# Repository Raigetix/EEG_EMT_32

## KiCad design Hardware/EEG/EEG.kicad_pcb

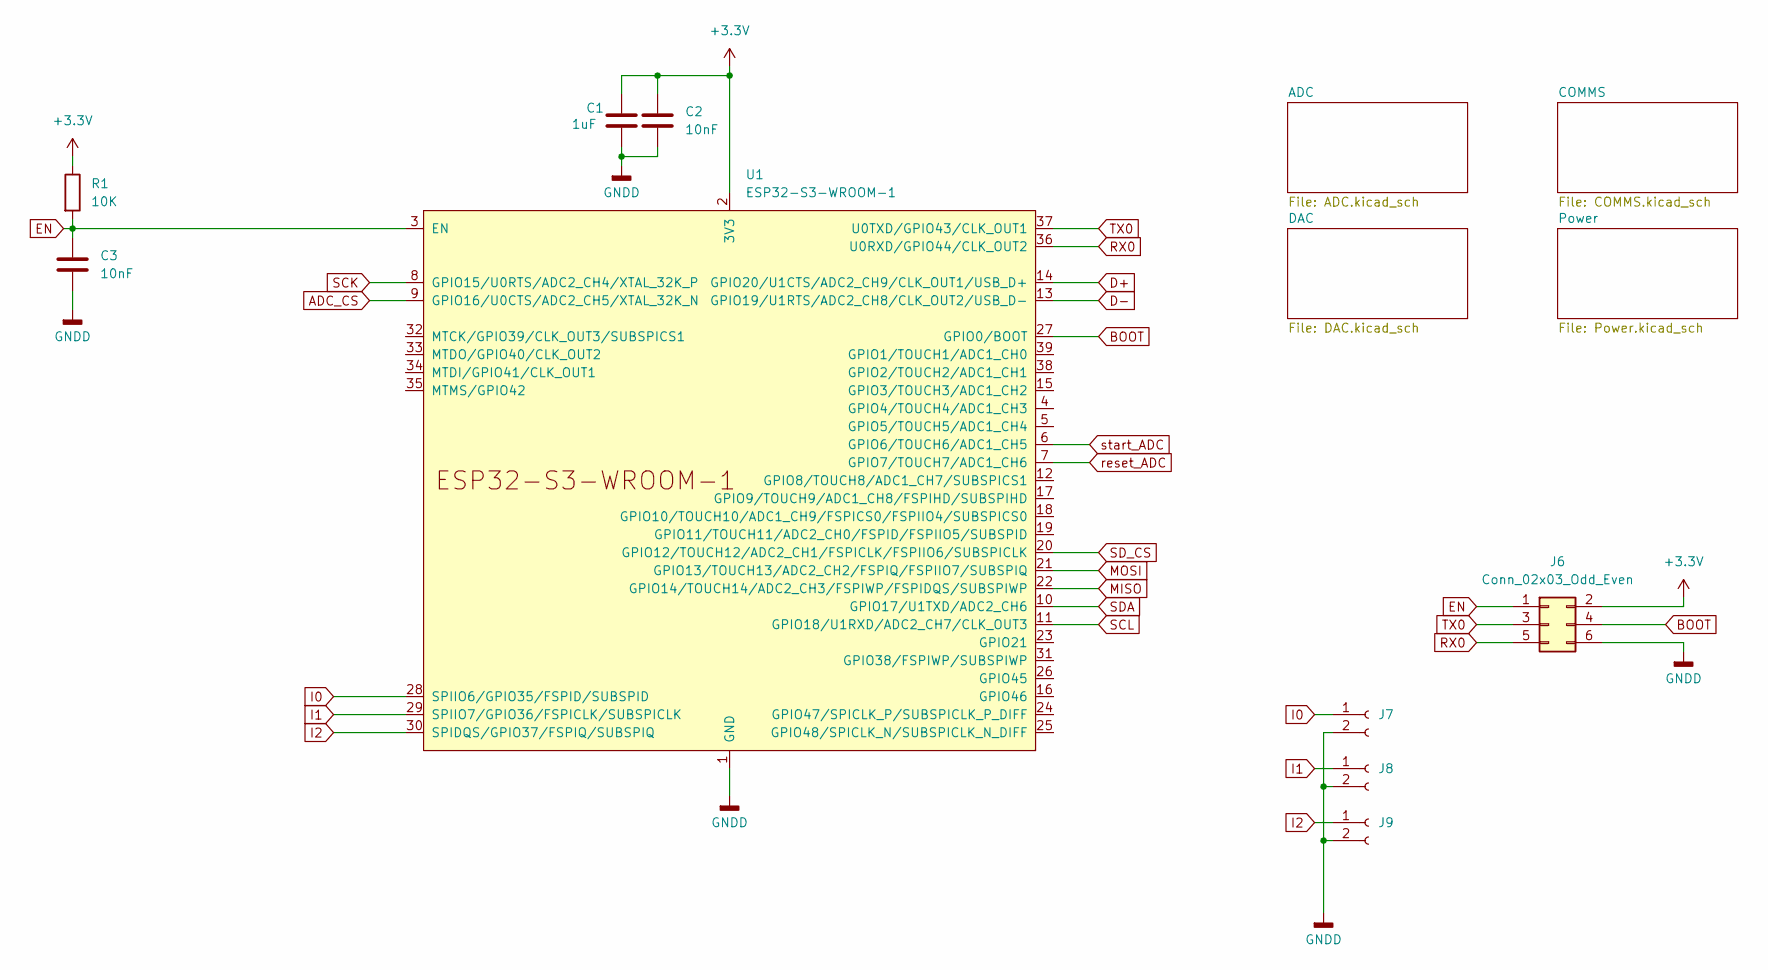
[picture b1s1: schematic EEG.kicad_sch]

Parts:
C1: 1uF; C_1210_3225Metric_Pad1.33x2.70mm_HandSolder
C2, C3: 10nF; C_0603_1608Metric_Pad1.08x0.95mm_HandSolder
J6: Conn_02x03_Odd_Even; PinHeader_2x03_P2.54mm_Vertical
J7, J8, J9: Conn_01x02_Socket; JST_XA_B02B-XASK-1-A_1x02_P2.50mm_Vertical
R1: 10K; R_0402_1005Metric_Pad0.72x0.64mm_HandSolder
U1: ESP32-S3-WROOM-1

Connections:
+3.3V: C1.1, C2.1, J6.2, R1.1, U1.2 (3V3); also elsewhere on the board
ADC_CS: U1.9 (GPIO16/U0CTS/ADC2_CH5/XTAL_32K_N); also elsewhere on the board
BOOT: J6.4, U1.27 (GPIO0/BOOT)
D+: U1.14 (GPIO20/U1CTS/ADC2_CH9/CLK_OUT1/USB_D+); also elsewhere on the board
D-: U1.13 (GPIO19/U1RTS/ADC2_CH8/CLK_OUT2/USB_D-); also elsewhere on the board
EN: C3.1, J6.1, R1.2, U1.3 (EN)
GNDA: C1.2, C2.2, C3.2, J6.6, J7.2, J8.2, J9.2, U1.1 (GND), U1.40 (GND), U1.41 (GND); also elsewhere on the board
I0: J7.1, U1.28 (SPIIO6/GPIO35/FSPID/SUBSPID)
I1: J8.1, U1.29 (SPIIO7/GPIO36/FSPICLK/SUBSPICLK)
I2: J9.1, U1.30 (SPIDQS/GPIO37/FSPIQ/SUBSPIQ)
MISO: U1.22 (GPIO14/TOUCH14/ADC2_CH3/FSPIWP/FSPIDQS/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); also elsewhere on the board
MOSI: U1.21 (GPIO13/TOUCH13/ADC2_CH2/FSPIQ/FSPIIO7/S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); also elsewhere on the board
RX0: J6.5, U1.36 (U0RXD/GPIO44/CLK_OUT2)
SCK: U1.8 (GPIO15/U0RTS/ADC2_CH4/XTAL_32K_P); also elsewhere on the board
SCL: U1.11 (GPIO18/U1RXD/ADC2_CH7/CLK_OUT3); also elsewhere on the board
SDA: U1.10 (GPIO17/U1TXD/ADC2_CH6); also elsewhere on the board
SD_CS: U1.20 (GPIO12/TOUCH12/ADC2_CH1/FSPICLK/FSPIIO6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); also elsewhere on the board
TX0: J6.3, U1.37 (U0TXD/GPIO43/CLK_OUT1)
reset_ADC: U1.7 (GPIO7/TOUCH7/ADC1_CH6); also elsewhere on the board
start_ADC: U1.6 (GPIO6/TOUCH6/ADC1_CH5); also elsewhere on the board

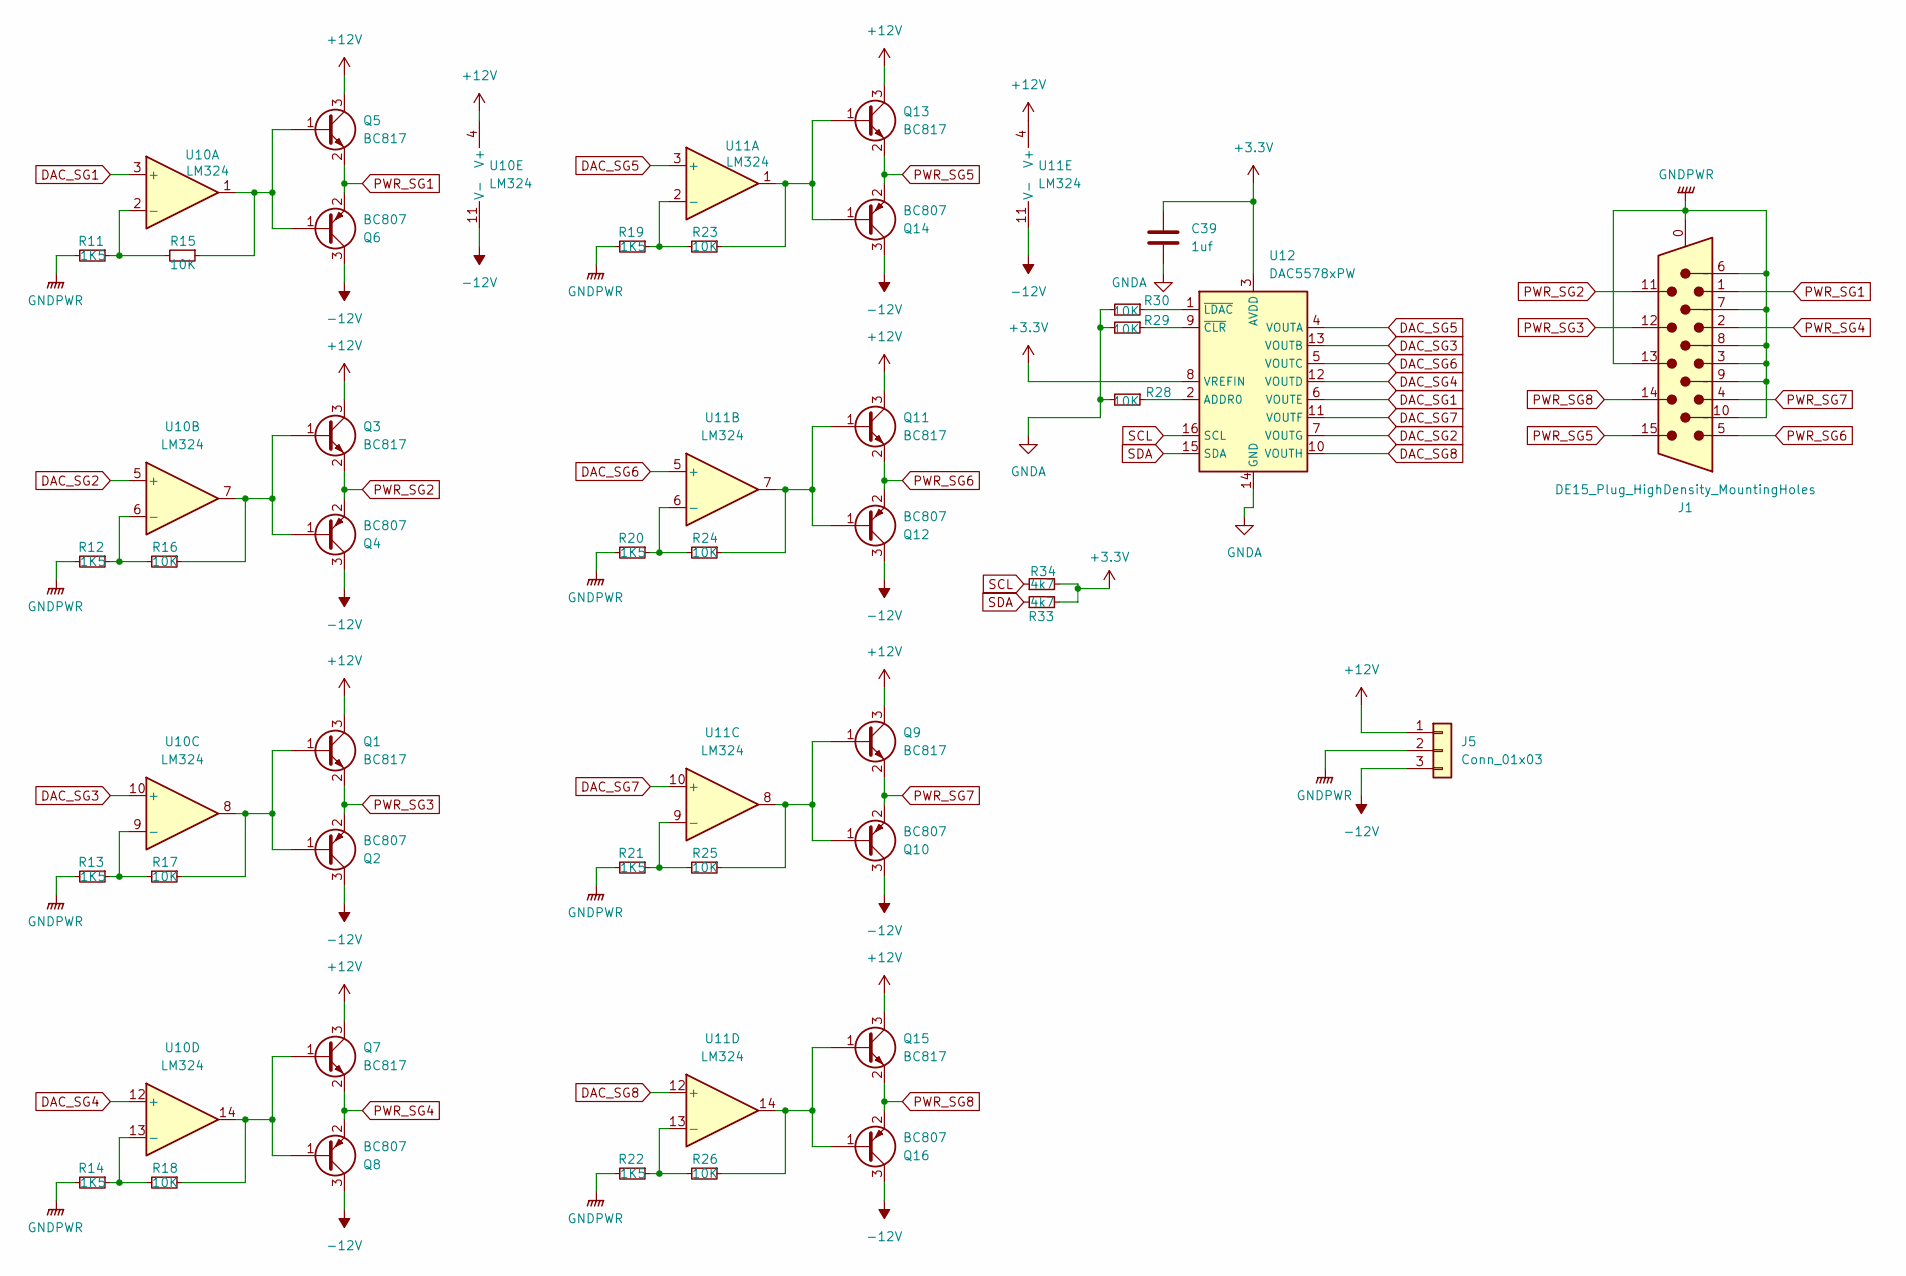
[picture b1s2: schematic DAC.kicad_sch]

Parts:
C39: 1uf; C_0603_1608Metric_Pad1.08x0.95mm_HandSolder
J1: DE15_Plug_HighDensity_MountingHoles; DSUB-15-HD_Female_Horizontal_P2.29x1.98mm_EdgePinOffset3.03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
J5: Conn_01x03; TerminalBlock_Phoenix_MKDS-1,5-3_1x03_P5.00mm_Horizontal
Q1, Q3, Q5, Q7, Q9, Q11, Q13, Q15: BC817; SOT-23
Q2, Q4, Q6, Q8, Q10, Q12, Q14, Q16: BC807; SOT-23
R11, R12, R13, R14, R19, R20, R21, R22: 1K5; R_0402_1005Metric_Pad0.72x0.64mm_HandSolder
R15, R16, R17, R18, R23, R24, R25, R26, R28, R29, R30: 10K; R_0402_1005Metric_Pad0.72x0.64mm_HandSolder
R33, R34: 4k7; R_0402_1005Metric_Pad0.72x0.64mm_HandSolder
U10, U11: LM324; TSSOP-14_4.4x5mm_P0.65mm
U12: DAC5578xPW; TSSOP-16_4.4x5mm_P0.65mm

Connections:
+3.3V: C39.1, R33.2, R34.2, U12.3 (AVDD), U12.8 (VREFIN); also elsewhere on the board
+12V: J5.1, Q1.3 (C), Q3.3 (C), Q5.3 (C), Q7.3 (C), Q9.3 (C), Q11.3 (C), Q13.3 (C), Q15.3 (C), U10.4 (V+), U11.4 (V+)
-12V: J5.3, Q2.3 (C), Q4.3 (C), Q6.3 (C), Q8.3 (C), Q10.3 (C), Q12.3 (C), Q14.3 (C), Q16.3 (C), U10.11 (V-), U11.11 (V-)
DAC_SG1: U10.3 (+), U12.6 (VOUTE)
DAC_SG2: U10.5 (+), U12.7 (VOUTG)
DAC_SG3: U10.10 (+), U12.13 (VOUTB)
DAC_SG4: U10.12 (+), U12.12 (VOUTD)
DAC_SG5: U11.3 (+), U12.4 (VOUTA)
DAC_SG6: U11.5 (+), U12.5 (VOUTC)
DAC_SG7: U11.10 (+), U12.11 (VOUTF)
DAC_SG8: U11.12 (+), U12.10 (VOUTH)
GNDA: C39.2, J1.0, J1.3, J1.6, J1.7, J1.8, J1.9, J1.10, J1.13, J5.2, R11.2, R12.2, R13.2, R14.2, R19.2, R20.2, R21.2, R22.2, R28.2, R29.2, R30.2, U12.14 (GND); also elsewhere on the board
unnamed: Q1.1 (B), Q2.1 (B), R17.1, U10.8
unnamed: Q3.1 (B), Q4.1 (B), R16.1, U10.7
unnamed: Q5.1 (B), Q6.1 (B), R15.1, U10.1
unnamed: Q7.1 (B), Q8.1 (B), R18.1, U10.14
unnamed: Q9.1 (B), Q10.1 (B), R25.1, U11.8
unnamed: Q11.1 (B), Q12.1 (B), R24.1, U11.7
unnamed: Q13.1 (B), Q14.1 (B), R23.1, U11.1
unnamed: Q15.1 (B), Q16.1 (B), R26.1, U11.14
unnamed: R11.1, R15.2, U10.2 (-)
unnamed: R12.1, R16.2, U10.6 (-)
unnamed: R13.1, R17.2, U10.9 (-)
unnamed: R14.1, R18.2, U10.13 (-)
unnamed: R19.1, R23.2, U11.2 (-)
unnamed: R20.1, R24.2, U11.6 (-)
unnamed: R21.1, R25.2, U11.9 (-)
unnamed: R22.1, R26.2, U11.13 (-)
unnamed: R28.1, U12.2 (ADDR0)
unnamed: R29.1, U12.9 (~CLR)
unnamed: R30.1, U12.1 (~LDAC)
PWR_SG1: J1.1, Q5.2 (E), Q6.2 (E)
PWR_SG2: J1.11, Q3.2 (E), Q4.2 (E)
PWR_SG3: J1.12, Q1.2 (E), Q2.2 (E)
PWR_SG4: J1.2, Q7.2 (E), Q8.2 (E)
PWR_SG5: J1.15, Q13.2 (E), Q14.2 (E)
PWR_SG6: J1.5, Q11.2 (E), Q12.2 (E)
PWR_SG7: J1.4, Q9.2 (E), Q10.2 (E)
PWR_SG8: J1.14, Q15.2 (E), Q16.2 (E)
SCL: R34.1, U12.16 (SCL); also elsewhere on the board
SDA: R33.1, U12.15 (SDA); also elsewhere on the board

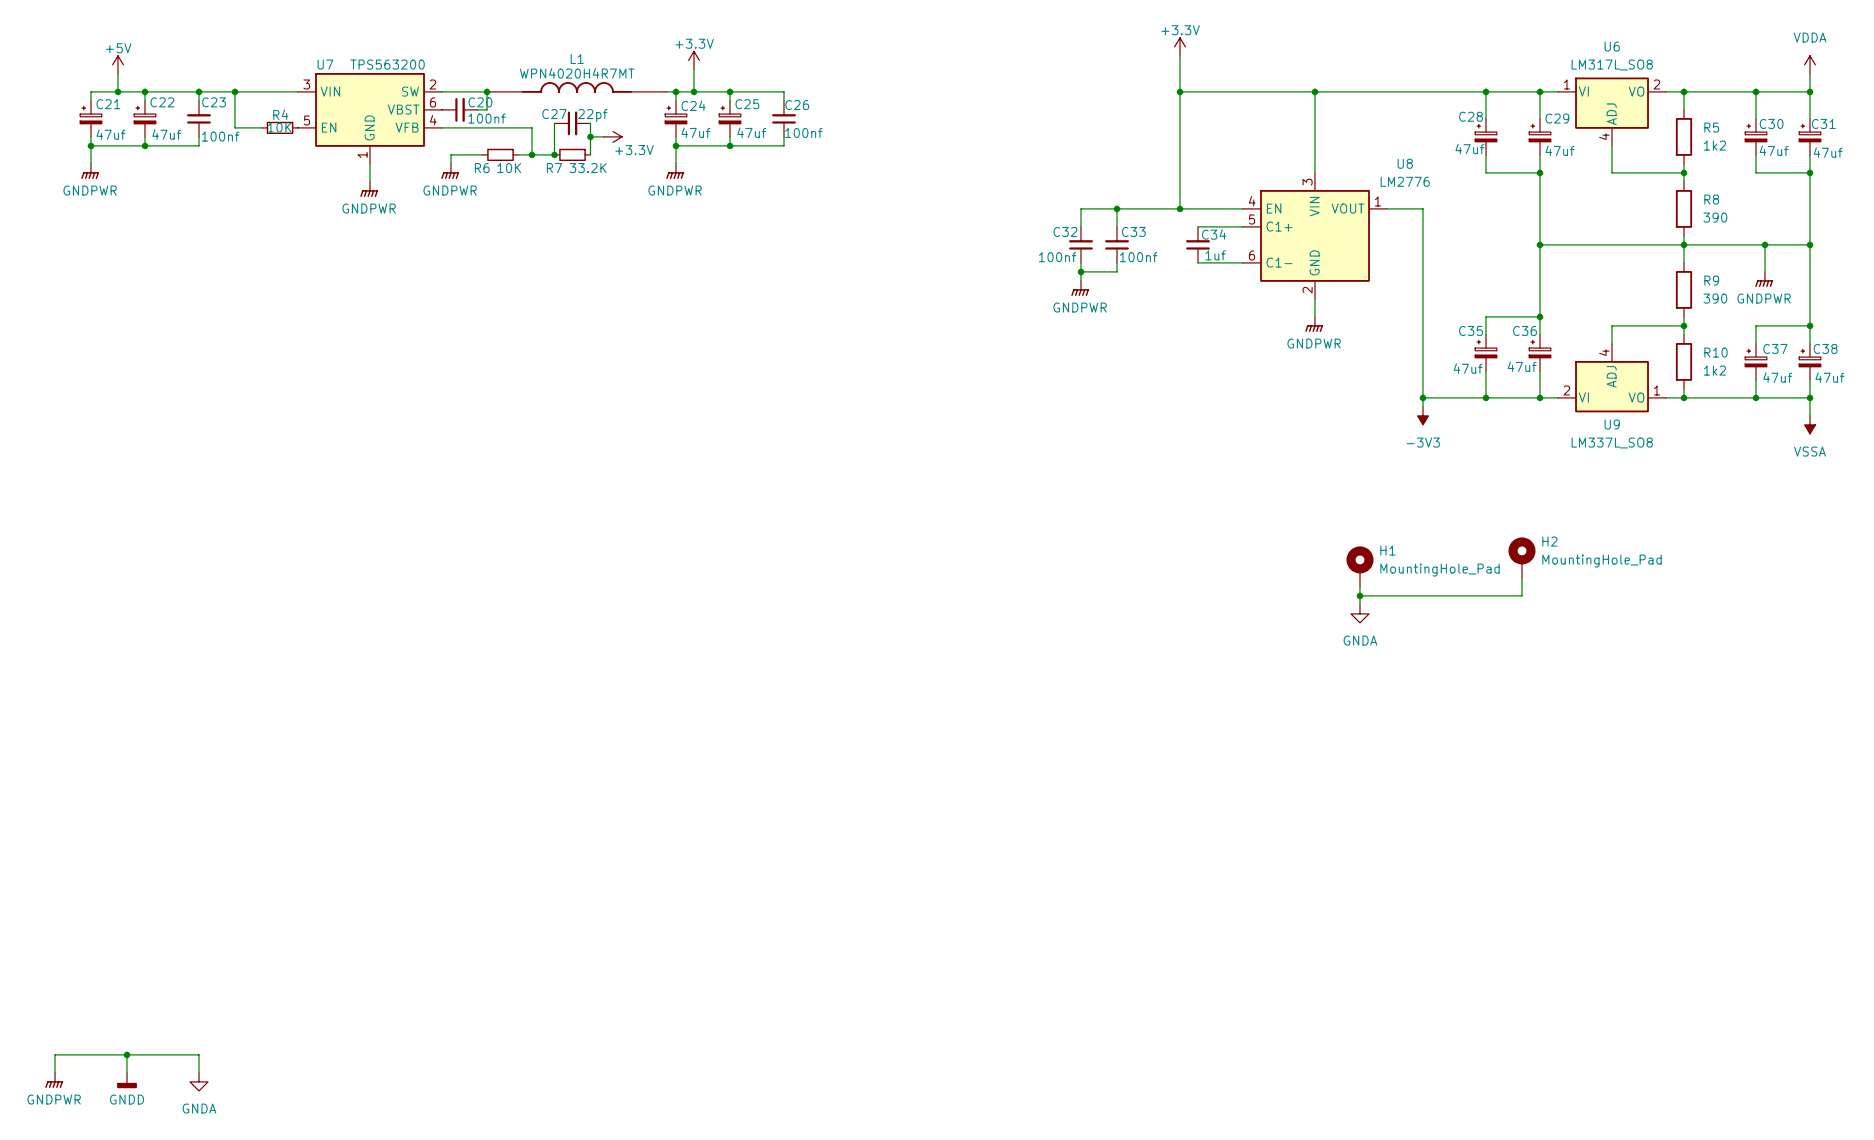
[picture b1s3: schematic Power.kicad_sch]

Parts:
C20, C23, C26, C32, C33: 100nf; L_0402_1005Metric_Pad0.77x0.64mm_HandSolder
C21, C22, C24, C25, C28, C29, C30, C31, C35, C36, C37, C38: 47uf; C_1210_3225Metric_Pad1.33x2.70mm_HandSolder
C27: 22pf; L_0402_1005Metric_Pad0.77x0.64mm_HandSolder
C34: 1uf; L_0402_1005Metric_Pad0.77x0.64mm_HandSolder
H1, H2: MountingHole_Pad; MountingHole_3.2mm_M3_Pad_Via
L1: WPN4020H4R7MT; L_Vishay_IFSC-1515AH_4x4x1.8mm; PARTREV 1
R4, R6: 10K; R_0402_1005Metric_Pad0.72x0.64mm_HandSolder
R5, R10: 1k2; R_0603_1608Metric_Pad0.98x0.95mm_HandSolder
R7: 33.2K; R_0402_1005Metric_Pad0.72x0.64mm_HandSolder
R8, R9: 390; R_0603_1608Metric_Pad0.98x0.95mm_HandSolder
U6: LM317L_SO8; SOIC-8_3.9x4.9mm_P1.27mm
U7: TPS563200; SOT-23-6
U8: LM2776; SOT-23-6
U9: LM337L_SO8; SOIC-8_3.9x4.9mm_P1.27mm

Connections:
+3.3V: C24.1, C25.1, C26.2, C27.2, C28.1, C29.1, C32.2, C33.2, L1.2, R7.1, U6.1 (VI), U8.3 (VIN), U8.4 (EN); also elsewhere on the board
+5V: C21.1, C22.1, C23.2, R4.2, U7.3 (VIN); also elsewhere on the board
-3V3: C35.2, C36.2, U8.1 (VOUT), U9.2 (VI), U9.3 (VI), U9.6 (VI), U9.7 (VI)
GNDA: C21.2, C22.2, C23.1, C24.2, C25.2, C26.1, C28.2, C29.2, C30.2, C31.2, C32.1, C33.1, C35.1, C36.1, C37.1, C38.1, H1.1, H2.1, R6.2, R8.2, R9.1, U7.1 (GND), U8.2 (GND); also elsewhere on the board
unnamed: R5.2, R8.1, U6.4 (ADJ)
unnamed: R4.1, U7.5 (EN)
unnamed: C20.2, L1.1, U7.2 (SW)
unnamed: C20.1, U7.6 (VBST)
unnamed: C27.1, R6.1, R7.2, U7.4 (VFB)
unnamed: C34.2, U8.5 (C1+)
unnamed: C34.1, U8.6 (C1-)
unnamed: R9.2, R10.1, U9.4 (ADJ)
VDDA: C30.1, C31.1, R5.1, U6.2 (VO), U6.3 (VO), U6.6 (VO), U6.7 (VO); also elsewhere on the board
VSSA: C37.2, C38.2, R10.2, U9.1 (VO); also elsewhere on the board

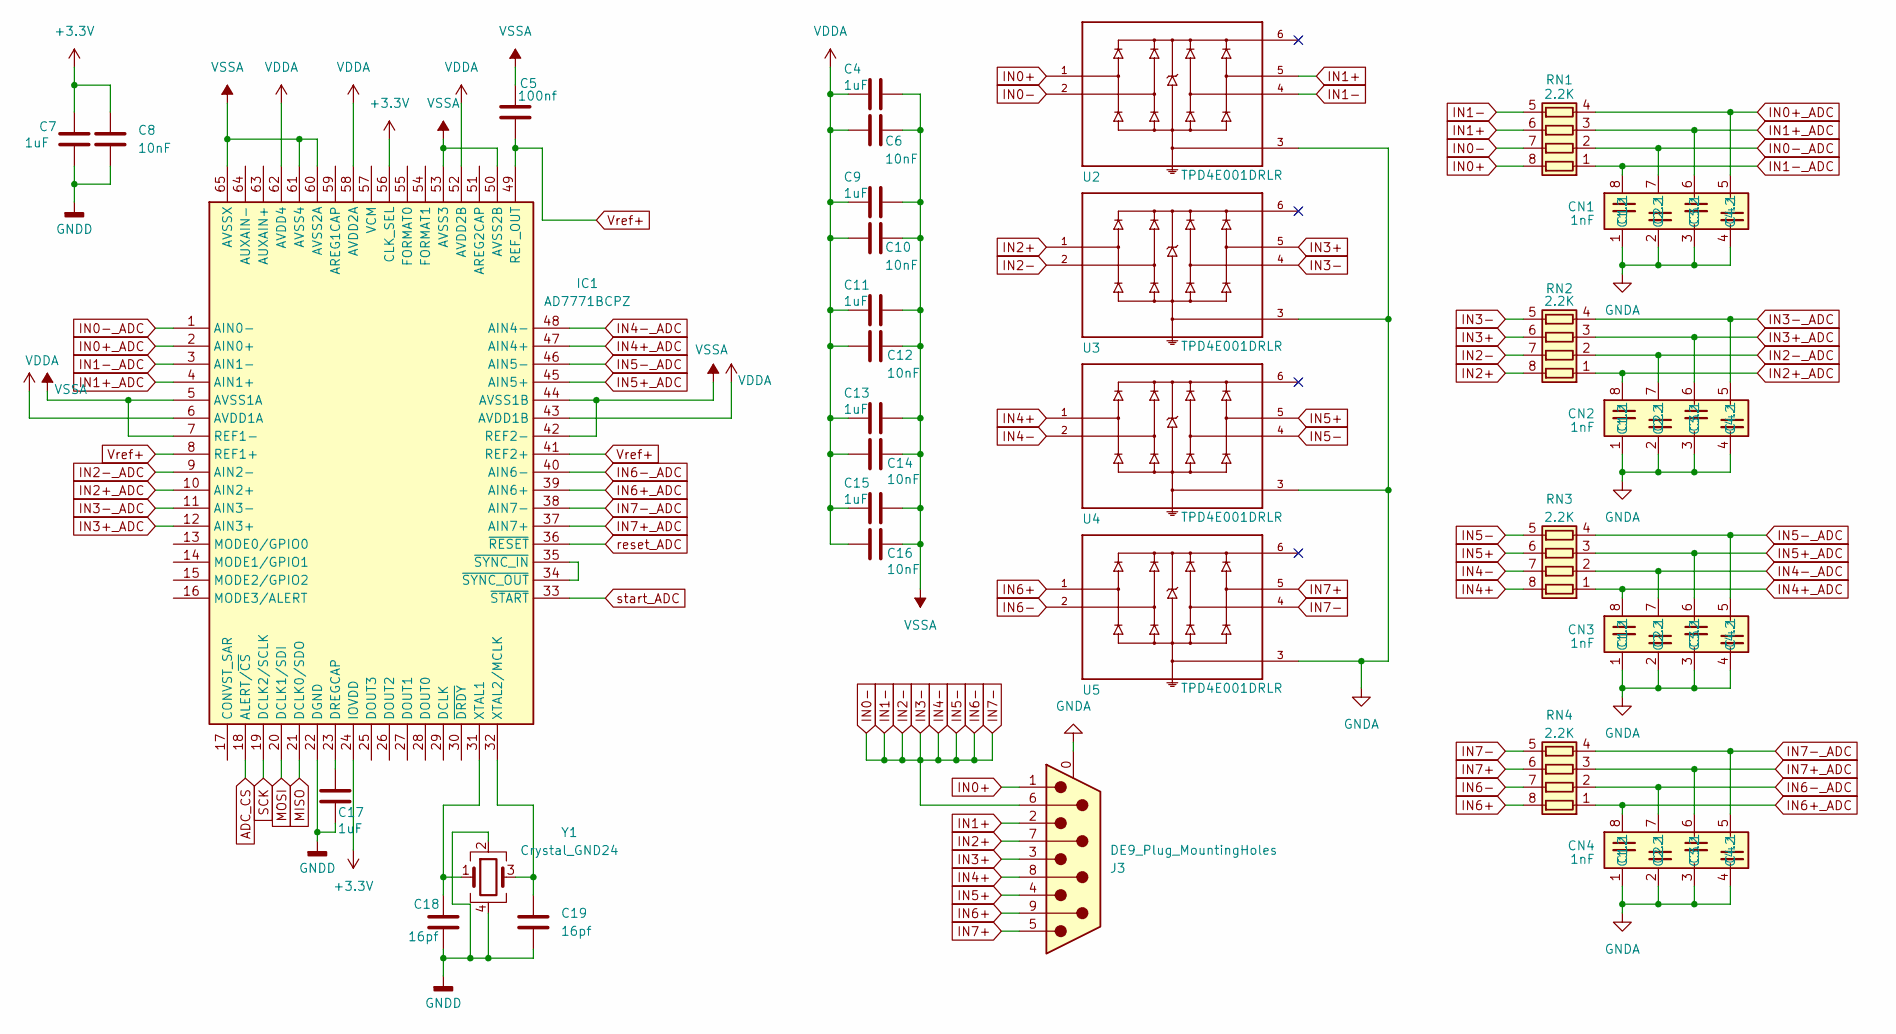
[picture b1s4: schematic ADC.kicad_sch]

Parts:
C4, C9, C11, C13, C15, C17: 1uF; C_0603_1608Metric_Pad1.08x0.95mm_HandSolder
C5: 100nf; C_0402_1005Metric_Pad0.74x0.62mm_HandSolder
C6, C8, C10, C12, C14, C16: 10nF; C_0603_1608Metric_Pad1.08x0.95mm_HandSolder
C7: 1uF; C_1210_3225Metric_Pad1.33x2.70mm_HandSolder
C18, C19: 16pf; C_0402_1005Metric_Pad0.74x0.62mm_HandSolder
CN1: 1nF; R_Array_Convex_4x0603
CN2, CN3, CN4: 1nF; R_Array_Concave_4x0603
IC1: AD7771BCPZ; QFN-64-1EP_9x9mm_P0.5mm_EP7.35x7.35mm; Manufacturer_Part_Number AD7771BCPZ; Mouser Part Number 584-AD7771BCPZ
J3: DE9_Plug_MountingHoles; DSUB-9_Female_Horizontal_P2.77x2.84mm_EdgePinOffset4.94mm_H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
RN1, RN2, RN3, RN4: 2.2K; R_Array_Concave_4x0603
U2, U3, U4, U5: TPD4E001DRLR; Texas_R-PDSO-N6_DRL-6
Y1: Crystal_GND24; Crystal_SMD_SeikoEpson_FA238V-4Pin_3.2x2.5mm

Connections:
+3.3V: C7.1, C8.1, IC1.24 (IOVDD), IC1.56 (CLK_SEL); also elsewhere on the board
ADC_CS: IC1.18 (ALERT/~CS); also elsewhere on the board
GNDA: C7.2, C8.2, C17.2, C18.2, C19.2, CN1.1 (C1.1), CN1.2 (C2.1), CN1.3 (C3.1), CN1.4 (C4.1), CN2.1 (C1.1), CN2.2 (C2.1), CN2.3 (C3.1), CN2.4 (C4.1), CN3.1 (C1.1), CN3.2 (C2.1), CN3.3 (C3.1), CN3.4 (C4.1), CN4.1 (C1.1), CN4.2 (C2.1), CN4.3 (C3.1), CN4.4 (C4.1), IC1.22 (DGND), J3.0 (PAD), U2.3, U3.3, U4.3, U5.3, Y1.2, Y1.4; also elsewhere on the board
IN0+: J3.1, RN1.8 (R1.2), U2.1
IN0+_ADC: CN1.5 (C4.2), IC1.2 (AIN0+), RN1.4 (R4.1)
IN0-: J3.6, RN1.5 (R4.2), RN1.7 (R2.2), RN2.5 (R4.2), RN2.7 (R2.2), RN3.5 (R4.2), RN3.7 (R2.2), RN4.5 (R4.2), RN4.7 (R2.2), U2.2, U2.4, U3.2, U3.4, U4.2, U4.4, U5.2, U5.4
IN0-_ADC: CN1.7 (C2.2), IC1.1 (AIN0-), RN1.2 (R2.1)
IN1+: J3.2, RN1.6 (R3.2), U2.5
IN1+_ADC: CN1.6 (C3.2), IC1.4 (AIN1+), RN1.3 (R3.1)
IN1-_ADC: CN1.8 (C1.2), IC1.3 (AIN1-), RN1.1 (R1.1)
IN2+: J3.7, RN2.8 (R1.2), U3.1
IN2+_ADC: CN2.8 (C1.2), IC1.10 (AIN2+), RN2.1 (R1.1)
IN2-_ADC: CN2.7 (C2.2), IC1.9 (AIN2-), RN2.2 (R2.1)
IN3+: J3.3, RN2.6 (R3.2), U3.5
IN3+_ADC: CN2.6 (C3.2), IC1.12 (AIN3+), RN2.3 (R3.1)
IN3-_ADC: CN2.5 (C4.2), IC1.11 (AIN3-), RN2.4 (R4.1)
IN4+: J3.8, RN3.8 (R1.2), U4.1
IN4+_ADC: CN3.8 (C1.2), IC1.47 (AIN4+), RN3.1 (R1.1)
IN4-_ADC: CN3.7 (C2.2), IC1.48 (AIN4-), RN3.2 (R2.1)
IN5+: J3.4, RN3.6 (R3.2), U4.5
IN5+_ADC: CN3.6 (C3.2), IC1.45 (AIN5+), RN3.3 (R3.1)
IN5-_ADC: CN3.5 (C4.2), IC1.46 (AIN5-), RN3.4 (R4.1)
IN6+: J3.9, RN4.8 (R1.2), U5.1
IN6+_ADC: CN4.8 (C1.2), IC1.39 (AIN6+), RN4.1 (R1.1)
IN6-_ADC: CN4.7 (C2.2), IC1.40 (AIN6-), RN4.2 (R2.1)
IN7+: J3.5, RN4.6 (R3.2), U5.5
IN7+_ADC: CN4.6 (C3.2), IC1.37 (AIN7+), RN4.3 (R3.1)
IN7-_ADC: CN4.5 (C4.2), IC1.38 (AIN7-), RN4.4 (R4.1)
MISO: IC1.21 (DCLK0/SDO); also elsewhere on the board
MOSI: IC1.20 (DCLK1/SDI); also elsewhere on the board
unnamed: C17.1, IC1.23 (DREGCAP)
unnamed: C18.1, IC1.31 (XTAL1), Y1.1
unnamed: C19.1, IC1.32 (XTAL2/MCLK), Y1.3
unnamed: IC1.34 (~SYNC_OUT), IC1.35 (~SYNC_IN)
SCK: IC1.19 (DCLK2/SCLK); also elsewhere on the board
VDDA: C4.2, C6.2, C9.2, C10.2, C11.2, C12.2, C13.2, C14.2, C15.2, C16.2, IC1.6 (AVDD1A), IC1.43 (AVDD1B), IC1.52 (AVDD2B), IC1.58 (AVDD2A), IC1.62 (AVDD4); also elsewhere on the board
VSSA: C4.1, C5.1, C6.1, C9.1, C10.1, C11.1, C12.1, C13.1, C14.1, C15.1, C16.1, IC1.5 (AVSS1A), IC1.7 (REF1-), IC1.42 (REF2-), IC1.44 (AVSS1B), IC1.50 (AVSS2B), IC1.53 (AVSS3), IC1.60 (AVSS2A), IC1.61 (AVSS4), IC1.65 (AVSSX); also elsewhere on the board
Vref+: C5.2, IC1.8 (REF1+), IC1.41 (REF2+), IC1.49 (REF_OUT)
reset_ADC: IC1.36 (~RESET); also elsewhere on the board
start_ADC: IC1.33 (~START); also elsewhere on the board

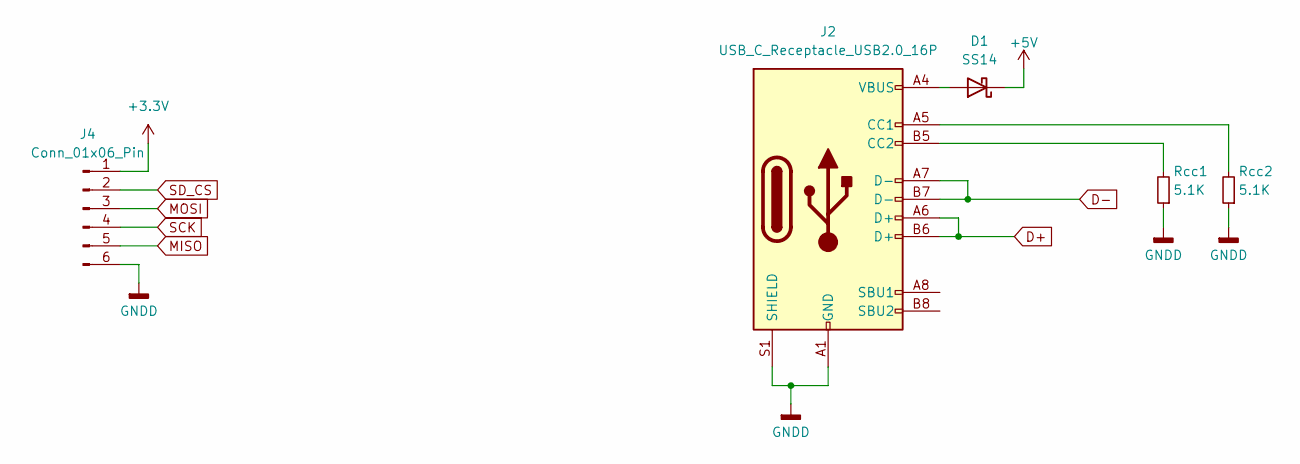
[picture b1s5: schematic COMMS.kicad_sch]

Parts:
D1: SS14; D_SMA
J2: USB_C_Receptacle_USB2.0_16P; USB_C_Receptacle_Palconn_UTC16-G
J4: Conn_01x06_Pin; PinHeader_1x06_P2.54mm_Vertical
Rcc1, Rcc2: 5.1K; R_0402_1005Metric_Pad0.72x0.64mm_HandSolder

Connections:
+3.3V: J4.1; also elsewhere on the board
+5V: D1.1 (K); also elsewhere on the board
D+: J2.A6 (D+), J2.B6 (D+); also elsewhere on the board
D-: J2.A7 (D-), J2.B7 (D-); also elsewhere on the board
GNDA: J2.A1 (GND), J2.A12 (GND), J2.B1 (GND), J2.B12 (GND), J2.S1 (SHIELD), J4.6, Rcc1.1, Rcc2.1; also elsewhere on the board
MISO: J4.5; also elsewhere on the board
MOSI: J4.3; also elsewhere on the board
unnamed: D1.2 (A), J2.A4 (VBUS), J2.A9 (VBUS), J2.B4 (VBUS), J2.B9 (VBUS)
unnamed: J2.A5 (CC1), Rcc2.2
unnamed: J2.B5 (CC2), Rcc1.2
SCK: J4.4; also elsewhere on the board
SD_CS: J4.2; also elsewhere on the board

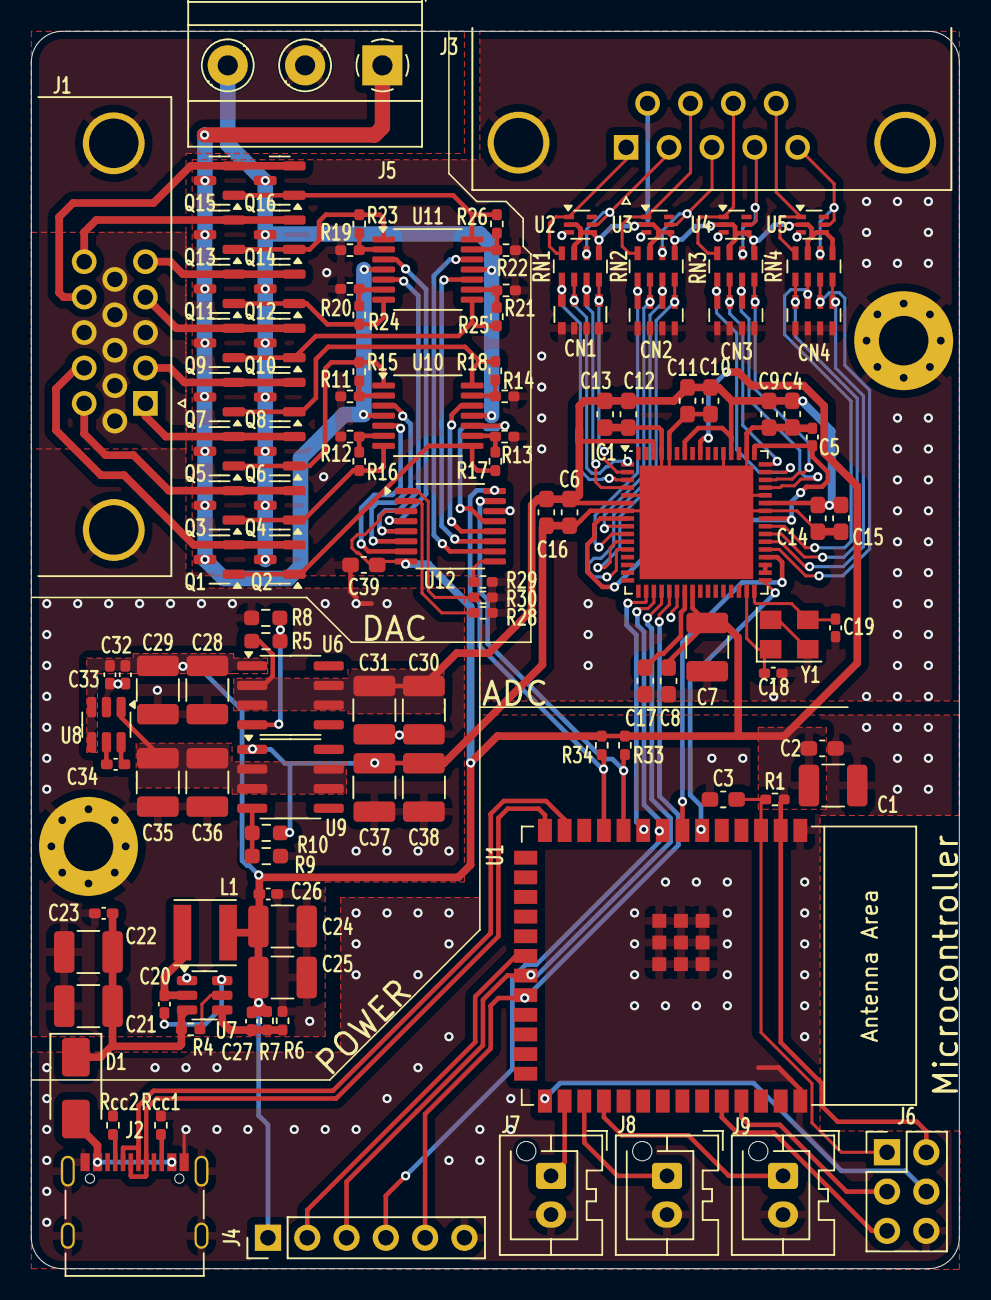
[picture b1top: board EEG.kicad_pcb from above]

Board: 2 copper layers, 60.0 x 80.0 mm, 121 parts (0 on the bottom side), 102 nets.

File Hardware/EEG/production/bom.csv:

Designator,Footprint,Quantity,Value,LCSC Part #
"C1, C7",1210,2,1uF,C393665
"C10, C12, C14, C16, C2, C3, C6, C8",0603,8,10nF,C519509
"C11, C13, C15, C9",0603,4,1uF,C106214
C17,0603,1,1uF,
"C18, C19",0402,2,16pf,C77590
"C20, C23, C26, C32, C33, C5",0402,6,100nf,C60474
"C21, C22, C24, C25, C28, C29, C30, C31, C35, C36, C37, C38",1210,12,47uf,C77101
C27,0402,1,22pf,C1555
C34,0402,1,1uf,C2887020
C39,0603,1,1uf,C1592
C4,0603,1,1uF,C106215
CN1,R_Array_Convex_4x0603,1,1nF,C62856
"CN2, CN3, CN4",R_Array_Concave_4x0603,3,1nF,C62856
D1,D_SMA,1,SS14,C266551
IC1,QFN-64-1EP_9x9mm_P0.5mm_EP7.35x7.35mm,1,AD7771BCPZ,C651536
J1,DSUB-15-HD_Female_Horizontal_P2.29x1.98mm_EdgePinOffset3.03mm_Housed_MountingHolesOffset4.94mm,1,DE15_Plug_HighDensity_MountingHoles,C75754
J2,USB_C_Receptacle_Palconn_UTC16-G,1,USB_C_Receptacle_USB2.0_16P,C136423
J3,DSUB-9_Female_Horizontal_P2.77x2.84mm_EdgePinOffset4.94mm_Housed_MountingHolesOffset7.48mm,1,DE9_Plug_MountingHoles,C75749
J5,"TerminalBlock_Phoenix_MKDS-1,5-3_1x03_P5.00mm_Horizontal",1,Conn_01x03,C91154
"J7, J8, J9",JST_XA_B02B-XASK-1-A_1x02_P2.50mm_Vertical,3,Conn_01x02_Socket,
L1,L_Vishay_IFSC-1515AH_4x4x1.8mm,1,WPN4020H4R7MT,C98363
"Q1, Q11, Q13, Q15, Q3, Q5, Q7, Q9",SOT-23,8,BC817,C146798
"Q10, Q12, Q14, Q16, Q2, Q4, Q6, Q8",SOT-23,8,BC807,C82369
"R1, R15, R16, R17, R18, R23, R24, R25, R26, R28, R29, R30, R4, R6",0402,14,10K,C71617
"R10, R5",0603,2,1k2,C114605
"R11, R12, R13, R14, R19, R20, R21, R22",0402,8,1K5,C114759
"R2, R3",0603,2,100,C110091
"R33, R34",0402,2,4k7,C105871
R7,0402,1,33.2K,C130276
"R8, R9",0603,2,390,C507432
"RCC1, RCC2",0402,2,5.1K,C144745
"RN1, RN2, RN3, RN4",R_Array_Concave_4x0603,4,2.2K,C414564
RV1,Potentiometer_Bourns_3266Y_Vertical,1,150,C83685
U1,ESP32-S3-WROOM-1,1,ESP32-S3-WROOM-1,C2913197
"U10, U11",TSSOP-14_4.4x5mm_P0.65mm,2,LM324,
U12,TSSOP-16_4.4x5mm_P0.65mm,1,DAC5578xPW,
"U2, U3, U4, U5",Texas_R-PDSO-N6_DRL-6,4,TPD4E001DRLR,C527516
U6,SOIC-8_3.9x4.9mm_P1.27mm,1,LM317L_SO8,C105219
U7,SOT-23-6,1,TPS563200,C97253
U8,SOT-23-6,1,LM2776,C840110
U9,SOIC-8_3.9x4.9mm_P1.27mm,1,LM337L_SO8,C544819
Y1,Crystal_SMD_SeikoEpson_FA238V-4Pin_3.2x2.5mm,1,Crystal_GND24,

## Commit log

2025-01-11 hardware update
2025-03-06 firmware update
2025-03-12 Compilacion, firmware para leer un solo canal de adc, falta test
2025-03-13 falta control de registros, hay que conectar drdy y sar conv para poder hacer la lectura bien
2025-03-19 por quinta vez se modifica libreria a lo de NO - OS, falta testing
2025-03-19 CORRECCION AD777x.cpp
